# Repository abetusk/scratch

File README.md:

scratch
=======

A scratch git repo for various experiments, random thoughts and other files that I want under source control but don't warrant their own repository.

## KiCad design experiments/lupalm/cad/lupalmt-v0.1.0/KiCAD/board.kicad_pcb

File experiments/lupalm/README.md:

lupalm
---

Dimmable palm light.

License
---

CC0

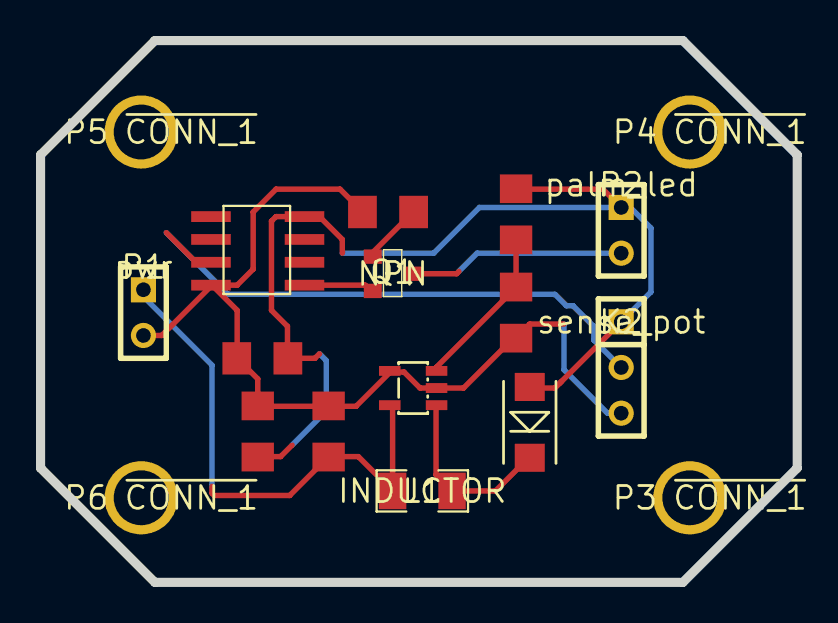
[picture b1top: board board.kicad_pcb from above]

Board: 5 copper layers, 42.0 x 30.1 mm, 18 parts (0 on the bottom side), 9 nets.

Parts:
C1: C; C1206
C2, C3: 1uF; C1206
D1: DIODE; DO-214AC
IC1: ATTINY13-P; SOIC-8
K2: sense_pot; SIL-3
L1: INDUCTOR; SM1206
P1: pwr; SIL-2
P2: palm_led; SIL-2
P3, P4, P5, P6: ~CONN_1; 1pin
Q1: NPN; SOT23
R1, R2, R3: R; R1206
U3: IC_FAN5331-SOT-23-5_SOT-23-5; SOT-23-5

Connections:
unnamed: C1.1, C2.1, D1.2, IC1.8, K2.1, P2.1, R2.1
unnamed: P2.2, Q1.3
unnamed: IC1.3, K2.2
unnamed: C1.2, C2.2, C3.2, IC1.4, K2.3, P1.2, R1.2, R3.2, U3.2, U3.4
unnamed: IC1.5, Q1.2
unnamed: Q1.1, R1.1
unnamed: D1.1, L1.2, U3.1
unnamed: R2.2, R3.1, U3.3
unnamed: C3.1, L1.1, P1.1, U3.5

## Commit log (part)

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2022-12-17 math formatting
2023-01-04 fighting with LaTeX markdown
2023-09-08 bms paper notes (personal)
2023-09-20 spelling
2023-10-29 obj2gnuplot
    * tiny_obj_loader.h example
2023-10-29 obj2stl
2023-11-05 adding pause, adjusting bpm
2024-01-04 img formatting
2024-04-17 partial matches for reminder
2024-05-06 updating starred list
2024-07-15 wip ...
2024-07-15 wip
    ...
2024-07-22 wip
    incrementally getting there
2024-07-22 minigolf gltf
2024-07-22 obj merge
2024-07-23 bug fixes, updates, refactor
    * moved obj merge and transform into jeom
    * fixed transform bug in obj transform to not move normals
    * fixed merge bug from swapping vt and vn (vt comes before vn in f, fixed now)
    * stickem uses negative angles
    * stickem and osajust use jeom for obj (simple) manipulation
2024-07-23 wip
    * working through issues with sticke_minigolf.conf
    - fixing up docks
2024-07-23 docking pairs
2024-07-23 originals before translation
2024-07-23 fiddling with weights
2024-07-24 cityroads obj + mtl files
2024-07-25 fixing up plum
2024-07-25 wip
    * fixing up some docking issues on plum arch
    * empty stl so f3d doesn't complain when trying to display empty tiles
    * ':' tile for wild card tile element
    * minor formatting
2024-07-25 wip
    * something wrong with plumarch poms creation, workingon fixing it
2024-07-25 wip
    * debugging plum-arch
2024-07-26 wip
    * plum arch looks to be working
    * need to check minigolf
    * cleaned up stickem to remove all 3d geom docking stuff
    * changed '!' docking type (gobble) so that you can specify
    source name type. Still not idea but gets to the place
    I needed to be with plum arch (for block joins)
2024-07-26 wip
    * bug in arch2 (maybe other archs). Does not realize. tracking down
2024-07-26 rename
2024-07-26 arch0 needs lower left as reference, not middle
2024-07-29 wip
    * looks to be working
2024-07-30 experimentation
2024-07-31 fixing ground and empty tile so it doesn't complain with visualizer
2024-07-31 fiddling with stair path
2024-07-31 working path for brutal plum
2024-08-01 wip
    * 1path and 2path brutal plum
2024-08-01 meh stars
2024-08-01 brutal plum loops working
    * still a bit unclear why we need to put the caps in a bit, putting
    them at [0,1,1] and [1,1,0] doesn't work, we need to put them
    at [1,1,2] and [2,1,1] (and in a bit on the the other corner as well)
2024-08-02 wip
    * fiddling with masks
    - since its 2d, there will always be a path cutoff (left/right, top/bottom),
    so we just need to understand it and mitigate the visual hint
2024-08-02 wip
    * still a bug, failing to setup
2024-08-02 bug fix?
2024-08-02 bug fix
    * dock partner was always evaluated, even when docks were simple.
    - fix not great but hacked something together
2024-08-04 removing cruft
2024-08-05 simple brutal plum, add ground constraints
2024-08-05 wip brutal plum
    playing with probabilities, looking better
2024-08-05 wip
    brutal plum fiddling
2024-08-05 wip
    * probability fiddling for paths
2024-08-07 fiddling with paths
2024-08-08 no debugging geometry
2024-10-18 sotto for buried tasks
2025-04-16 two.js
2025-10-21 readme and license
2025-12-15 bard
2025-12-19 kb layout
2025-12-19 svg image display
    table scales the svg down
2025-12-22 experimenting...
2026-04-08 loop and tension parameter for hobby curve helper function
2026-04-20 example
2026-04-20 aux lib
2026-04-20 adding reference
2026-05-26 funcdef working?
    pretty janky
2026-05-27 fibonacci function
2026-05-28 cond
    ...
2026-06-03 bug
    * recursive calls blow the stack
2026-06-10 bug fix
    * needed calling environment for parameter evaluation
    of lambda call
2026-06-29 prepping
2026-06-29 working on mobile integration (still not working)
2026-06-29 progress
